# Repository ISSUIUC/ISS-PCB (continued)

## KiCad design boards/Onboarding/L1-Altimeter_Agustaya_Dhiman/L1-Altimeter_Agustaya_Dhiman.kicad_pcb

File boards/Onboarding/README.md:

# Onboarding Projects

The included projects have been developed for the purpose of teaching new members about the basics of circuit design and using KiCad.

The first project includes a 555 Timer that is used to flash several LEDs in combination with an N-channel MOSFET. This project is accompanied by other onboarding materials which explain how to use the 555 Timer and develop the circuit. There are also videos going through the [schematic](https://youtu.be/EWncukrDE1s) and [layout](https://youtu.be/gsBfX4-ESjE) design.

The second project is a basic two layer altimeter that could be used in an L1 rocket. It is intended to be more open-ended, and the included design can serve as merely an example. The altimeter includes an MCU, sensors connected via the SPI and I2C communication protocols, a microSD card for data storage, and basic power circuitry that can be used with an external voltage regulator. Extra GPIOs are broken out for future expansions.

# Schematics

Printable PDF schematics can be found in the folders for their respective boards.

# Renders

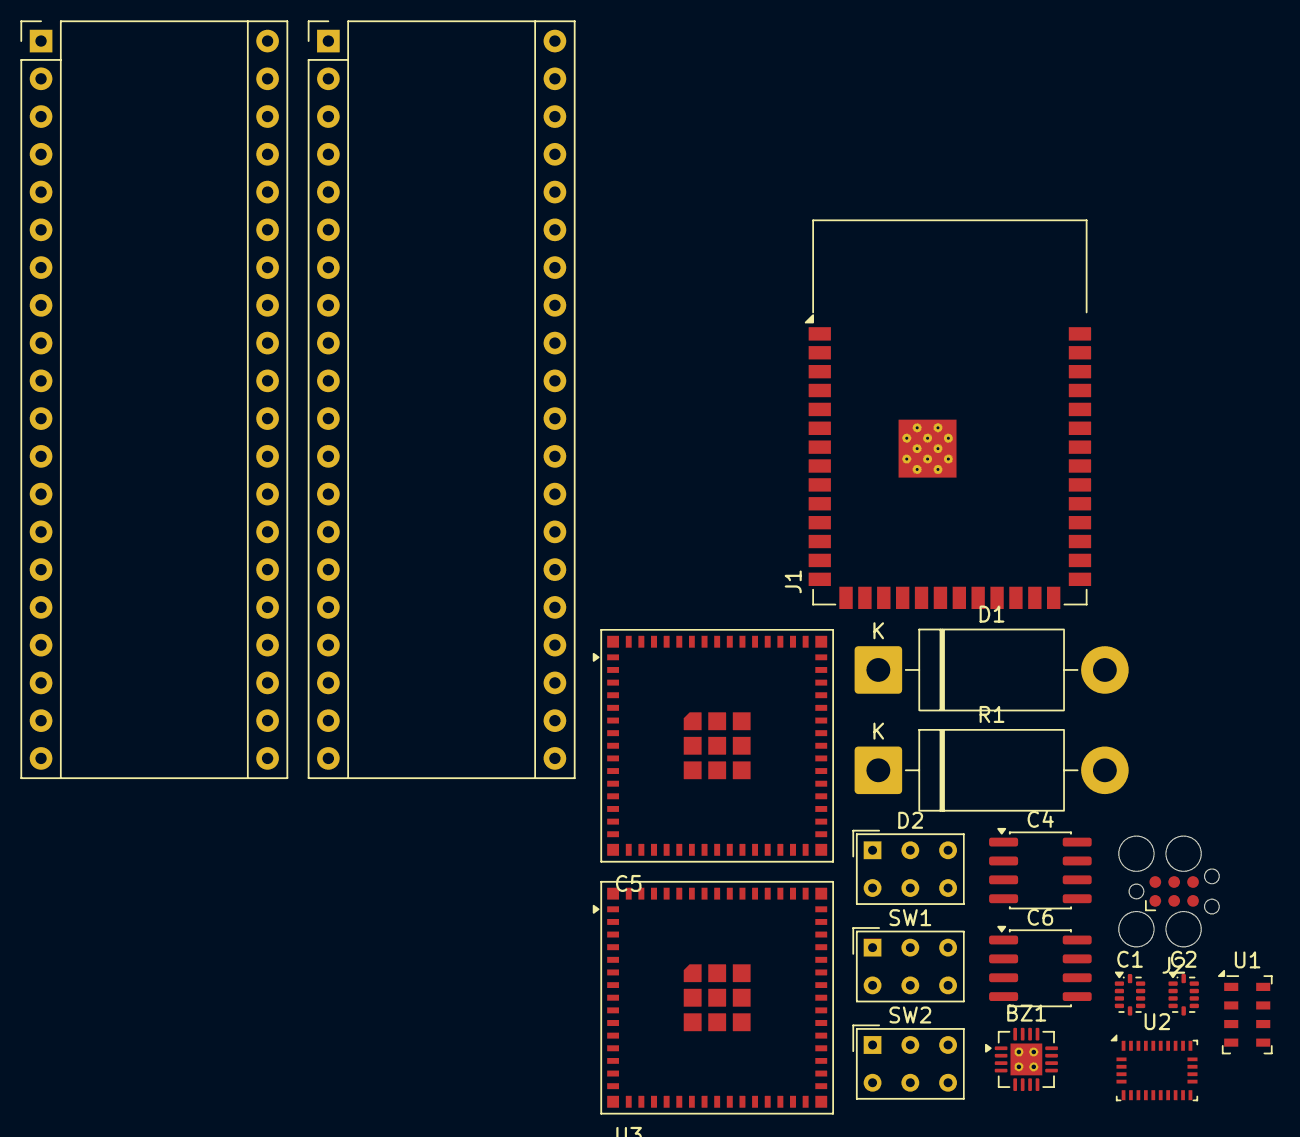
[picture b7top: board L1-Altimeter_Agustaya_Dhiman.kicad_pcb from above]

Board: 2 copper layers, 18 parts (0 on the bottom side), 9 nets, no tracks yet.

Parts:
BZ1: Buzzer; Texas_RVA_VQFN-16-1EP_3.5x3.5mm_P0.5mm_EP2.14x2.14mm_Therma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
C1, C2: .1uF; Balun_Johanson_0900PC15J0013
C4, C6: .1uF; SOIC-8_3.9x4.9mm_P1.27mm
C5: .1uF; ESP32-S2-MINI-1U
D1: MBR340; D_DO-201AD_P15.24mm_Horizontal
D2: LED; SW_NKK_GW12LJP
H1: MountingHole; Maple_Mini
J1: USB_A; ESP32-S3-WROOM-1
J2: Screw_Terminal_01x04; Tag-Connect_TC2030-IDC-FP_2x03_P1.27mm_Vertical
J10: DM3D-SF; Maple_Mini
R1: 100K; D_DO-201AD_P15.24mm_Horizontal
SW1, SW2: SW_Push; SW_NKK_GW12LJP
U1: MS5611-01BA; LGA-8_3x5mm_P1.25mm
U2: BNO086; LGA-28_5.2x3.8mm_P0.5mm
U3: ESP32-S3-MINI-1U; ESP32-S2-MINI-1U

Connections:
+3.3V: C6.1, U2.3 (VDD), U2.5 (PS1), U2.28 (VDDIO)
+3V3: C4.1, J10.4 (VDD), U1.1 (VDD), U1.2 (PS), U2.10 (CLKSEL0)
/BOOT_SW: C1.1, SW1.1
/RESET_SW: C2.1, SW2.1
/VBUS: D1.2 (A), J1.1 (VBUS), R1.1
/VSYS: D1.1 (K), J2.2
GND: BZ1.2 (-), C1.2, C2.2, C4.2, C5.2, D2.1 (K), J1.4 (GND), J2.4, J10.6 (VSS), R1.2, SW1.2, SW2.2, U1.3 (GND), U1.4 (CSB), U1.5 (CSB), U2.2 (GND), U2.25 (GNDIO)
unnamed: C5.1, U2.9 (CAP)
unnamed: U3.1 (GND), U3.2 (GND), U3.42 (GND), U3.43 (GND), U3.46 (GND), U3.47 (GND), U3.48 (GND), U3.49 (GND), U3.50 (GND), U3.51 (GND), U3.52 (GND), U3.53 (GND), U3.54 (GND), U3.55 (GND), U3.56 (GND), U3.57 (GND), U3.58 (GND), U3.59 (GND), U3.60 (GND), U3.61 (GND), U3.62 (GND), U3.63 (GND), U3.64 (GND), U3.65 (GND)

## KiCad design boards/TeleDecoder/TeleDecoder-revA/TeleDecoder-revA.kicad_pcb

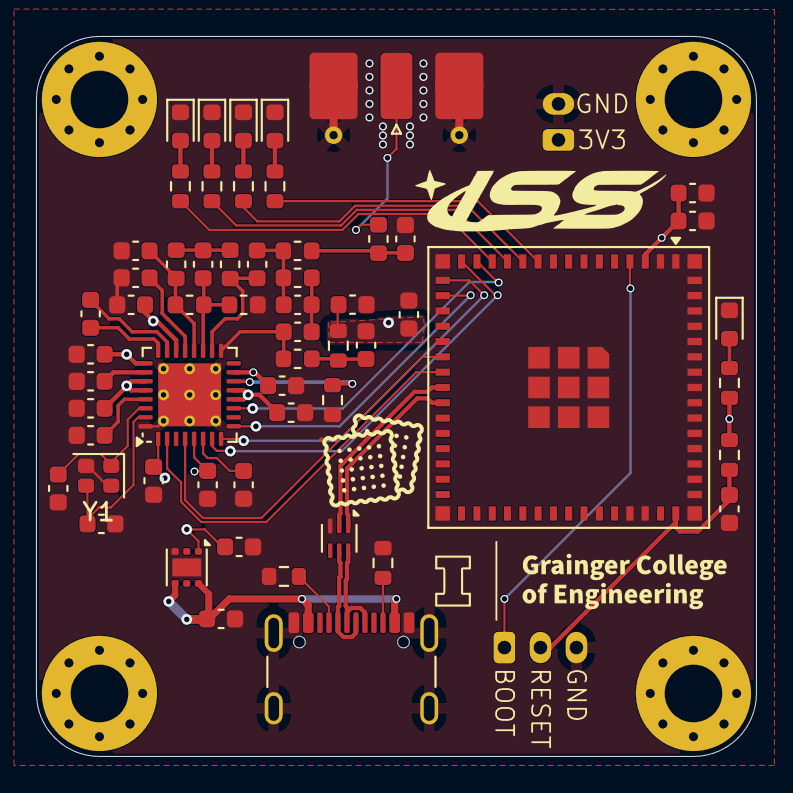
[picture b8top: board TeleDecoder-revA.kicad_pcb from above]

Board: 4 copper layers, 40.0 x 40.0 mm, 64 parts (0 on the bottom side), 45 nets.

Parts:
C1, C2, C127: 1uF; C_0603_1608Metric
C101: 22uF; C_0603_1608Metric
C102: 100nF; C_0603_1608Metric
C103, C119: 10nF; C_0603_1608Metric
C104: 56pF; C_0603_1608Metric
C105: 100pF; C_0603_1608Metric
C106: 39pF; C_0603_1608Metric
C107: 2.2pF; C_0603_1608Metric
C108, C109: 10pF; C_0603_1608Metric
C110, C111, C113: 5.1pF; C_0603_1608Metric
C112: 1.8nF; C_0603_1608Metric
C114: 6.2pF; C_0603_1608Metric
C115, C117, C118, C120, C121, C122, C123, C124, C125: 47nF; C_0603_1608Metric
C116: 220nF; C_0603_1608Metric
D101, D105: LED_RED; LED_0603_1608Metric
D102: LED_BLUE; LED_0603_1608Metric
D103: LED_GREEN; LED_0603_1608Metric
D104: LED_ORANGE; LED_0603_1608Metric
H101, H102, H103, H104: MountingHole; MountingHole_3.2mm_M3_Pad_Via
J101: Conn_01x03; JST_PH_B3B-PH-K_1x03_P2.00mm_Vertical
J102: USB4105-GF-A; USB_C_Receptacle_GCT_USB4105-xx-A_16P_TopMnt_Horizontal
J103: Conn_01x02; JST_PH_B2B-PH-K_1x02_P2.00mm_Vertical
J104: Conn_Coaxial; SMA_Molex_73251-2120_EdgeMount_Horizontal
L101, L102: 56nH; L_0603_1608Metric
L103, L106: 15nH; L_0603_1608Metric
L104, L105: 27nH; L_0603_1608Metric
L107: 43nH; L_0603_1608Metric
L108: 22nH; L_0603_1608Metric
R101, R102: 5.1k; R_0603_1608Metric
R103: 18; R_0603_1608Metric
R104: 56k; R_0603_1608Metric
R105, R106, R107, R108, R110: 470; R_0603_1608Metric
R109: 20k; R_0603_1608Metric
U101: ESP32-S3-MINI-1U; ESP32-S2-MINI-1U
U102: ECMF02-2AMX6; ST_UQFN-6L_1.5x1.7mm_P0.5mm
U103: CC1120; VQFN-32-1EP_5x5mm_P0.5mm_EP3.5x3.5mm_ThermalVias
U104: TPS746-Q1; WSON-6-1EP_2x2mm_P0.65mm_EP1x1.6mm
Y1: STDCZS3-40M; Crystal_SMD_2016-4Pin_2.0x1.6mm

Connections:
+3V3: C2.1, C101.1, C102.1, C103.1, C104.2, C105.1, C115.1, C117.1, C118.1, C120.1, C121.1, C123.1, C124.1, J103.1, R103.2, R109.2, R110.1, U101.3 (3V3), U103.1 (VDD_GUARD), U103.5 (DVDD), U103.12 (DVDD), U103.13 (AVDD_IF), U103.15 (AVDD_RF), U103.22 (AVDD_SYNTH1), U103.25 (AVDD_PFD_CHP), U103.27 (AVDD_SYNTH2), U103.28 (AVDD_XOSC), U104.1 (OUT)
+5V: C1.1, J102.A4 (VBUS), J102.A9 (VBUS), J102.B4 (VBUS), J102.B9 (VBUS), U104.4 (EN), U104.6 (IN)
/BOOT: J101.1, U101.4 (IO0)
/CS_RADIO: U101.14 (IO10), U103.11 (~CS)
/D+: J102.A6 (D+), J102.B6 (D+), U102.6 (D+_out)
/D-: J102.A7 (D-), J102.B7 (D-), U102.5 (D-_out)
/LED_BLUE: R106.1, U101.13 (IO9)
/LED_GREEN: R107.1, U101.12 (IO8)
/LED_ORANGE: R108.1, U101.11 (IO7)
/LED_RED: R105.1, U101.10 (IO6)
/LNA_N: C111.1, L102.2, L105.1, U103.20 (LNA_N)
/LNA_P: C110.1, L102.1, L104.1, U103.19 (LNA_P)
/MISO0: U101.17 (IO13), U103.9 (SO(GPIO1))
/MOSI0: U101.15 (IO11), U103.7 (SI)
/PA: C106.1, L101.1, U103.17 (PA)
/RADIO_INT: U101.21 (IO17), U103.4 (GPIO2)
/RESET: C127.1, J101.2, R109.1, U101.45 (EN)
/RESET_IN: U101.22 (IO18), U103.2 (~RESET)
/SCLK0: U101.16 (IO12), U103.8 (SCLK)
/TRX_SW: C113.1, L106.1, U103.18 (TRX_SW)
/USB_D+: U101.24 (USB_D+), U102.1 (D+_in)
/USB_D-: U101.23 (USB_D-), U102.2 (D-_in)
GND: C1.2, C2.2, C101.2, C102.2, C103.2, C105.2, C108.2, C109.2, C111.2, C114.2, C115.2, C116.2, C117.2, C118.2, C119.2, C120.2, C121.2, C122.2, C123.2, C124.2, C125.2, C127.2, D101.1 (K), D102.1 (K), D103.1 (K), D104.1 (K), D105.1 (K), J101.3, J102.A1 (GND), J102.A12 (GND), J102.B1 (GND), J102.B12 (GND), J102.S1 (SHIELD), J103.2, J104.2 (Ext), L104.2, R101.2, R102.2, R104.2, U101.1 (GND), U101.2 (GND), U101.42 (GND), U101.43 (GND), U101.46 (GND), U101.47 (GND), U101.48 (GND), U101.49 (GND), U101.50 (GND), U101.51 (GND), U101.52 (GND), U101.53 (GND), U101.54 (GND), U101.55 (GND), U101.56 (GND), U101.57 (GND), U101.58 (GND), U101.59 (GND), U101.60 (GND), U101.61 (GND), U101.62 (GND), U101.63 (GND), U101.64 (GND), U101.65 (GND), U102.3 (GND), U103.32 (EXT_XOSC), U103.33 (GND_EP), U104.3 (GND), U104.7 (EP), Y1.2
unnamed: C104.1, L101.2, R103.1
unnamed: C106.2, C107.1, L103.1
unnamed: C107.2, C113.2, L103.2, L107.1
unnamed: C110.2, L105.2, L106.2
unnamed: C114.1, L107.2, L108.1
unnamed: D101.2 (A), R105.2
unnamed: D102.2 (A), R106.2
unnamed: D103.2 (A), R107.2
unnamed: D104.2 (A), R108.2
unnamed: D105.2 (A), R110.2
unnamed: J102.A5 (CC1), R101.1
unnamed: J102.B5 (CC2), R102.1
unnamed: J104.1 (In), L108.2
unnamed: C116.1, U103.6 (DCPL)
unnamed: C122.1, U103.26 (DCPL_PFD_CHP)
unnamed: C119.1, U103.21 (DCPL_VCO)
unnamed: C125.1, U103.29 (DCPL_XOSC)
unnamed: C112.1, U103.23 (LPF0)
unnamed: C112.2, U103.24 (LPF1)
unnamed: R104.1, U103.14 (RBIAS)
unnamed: C108.1, U103.30 (XOSC_Q1), Y1.1
unnamed: C109.1, U103.31 (XOSC_Q2), Y1.3

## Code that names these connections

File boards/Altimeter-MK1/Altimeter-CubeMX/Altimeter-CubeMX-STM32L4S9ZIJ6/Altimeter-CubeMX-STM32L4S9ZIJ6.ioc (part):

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Mcu.Name=STM32L4S9ZIJx
Mcu.Package=UFBGA144
Mcu.UserName=STM32L4S9ZIJx
PA0.GPIOParameters=GPIO_Label
PA0.GPIO_Label=sense_e
PA0.Signal=ADCx_IN5
PA1.GPIOParameters=GPIO_Label
PA1.GPIO_Label=sense_f
PA1.Signal=ADCx_IN6
PA10.GPIOParameters=GPIO_Label
PA10.GPIO_Label=TELEM_CS
PA10.Signal=GPIO_Output
PA11.GPIOParameters=GPIO_Label
PA11.GPIO_Label=USB_DM
PA11.Mode=Device_Only
PA11.Signal=USB_OTG_FS_DM
PA12.GPIOParameters=GPIO_Label
PA12.GPIO_Label=USB_DP
PA12.Mode=Device_Only
PA12.Signal=USB_OTG_FS_DP
PA13\ (JTMS/SWDIO).GPIOParameters=GPIO_Label
PA13\ (JTMS/SWDIO).GPIO_Label=SWDIO
PA13\ (JTMS/SWDIO).Mode=Trace_Asynchronous_SW
PA13\ (JTMS/SWDIO).Signal=SYS_JTMS-SWDIO
PA14\ (JTCK/SWCLK).GPIOParameters=GPIO_Label
PA14\ (JTCK/SWCLK).GPIO_Label=SWSCLK
PA14\ (JTCK/SWCLK).Mode=Trace_Asynchronous_SW
PA14\ (JTCK/SWCLK).Signal=SYS_JTCK-SWCLK
PA15\ (JTDI).GPIOParameters=GPIO_Label
PA15\ (JTDI).GPIO_Label=RESERVED_JTDI
PA15\ (JTDI).Signal=SYS_JTDI
PA2.GPIOParameters=GPIO_Label
PA2.GPIO_Label=sense_vFlight
PA2.Signal=ADCx_IN7
PA3.GPIOParameters=GPIO_Label
PA3.GPIO_Label=sense_vPyro
PA3.Signal=ADCx_IN8
PA8.GPIOParameters=GPIO_Label
PA8.GPIO_Label=RESERVED_TIM1_CH1_PWM
PA8.Signal=S_TIM1_CH1
PA9.GPIOParameters=GPIO_Label
PA9.GPIO_Label=RESERVED_TIM1_CH2_PWM
PA9.Signal=S_TIM1_CH2
PB10.GPIOParameters=GPIO_Label
PB10.GPIO_Label=TELEM_SCK
PB10.Mode=Full_Duplex_Master
PB10.Signal=SPI2_SCK
PB15.GPIOParameters=GPIO_Label
PB15.GPIO_Label=TELEM_MOSI
PB15.Mode=Full_Duplex_Master
PB15.Signal=SPI2_MOSI
PB2.GPIOParameters=GPIO_Label
PB2.GPIO_Label=BUZZER_PWM
PB2.Mode=WaveformGeneration
PB2.Signal=LPTIM1_OUT
PB3\ (JTDO/TRACESWO).GPIOParameters=GPIO_Label
PB3\ (JTDO/TRACESWO).GPIO_Label=SWO
PB3\ (JTDO/TRACESWO).Mode=Trace_Asynchronous_SW
PB3\ (JTDO/TRACESWO).Signal=SYS_JTDO-SWO
PB4\ (NJTRST).GPIOParameters=GPIO_Label
PB4\ (NJTRST).GPIO_Label=RESERVED_PB4
PB4\ (NJTRST).Signal=SYS_JTRST
PB5.GPIOParameters=GPIO_Label
PB5.GPIO_Label=RESERVED_TIM3_CH2_PWM
PB5.Signal=S_TIM3_CH2
PB6.GPIOParameters=GPIO_Label
PB6.GPIO_Label=RESERVED_USART1_TX
PB6.Mode=Multiprocessor_communication
PB6.Signal=USART1_TX
PB7.GPIOParameters=GPIO_Label
PB7.GPIO_Label=RESERVED_USART1_RX
PB7.Mode=Multiprocessor_communication
PB7.Signal=USART1_RX
PB8.GPIOParameters=GPIO_Label
PB8.GPIO_Label=LED_BLUE
PB8.Signal=GPIO_Output
PB9.GPIOParameters=GPIO_Label
PB9.GPIO_Label=LED_ORANGE
PB9.Signal=GPIO_Output
PC0.GPIOParameters=GPIO_Label
PC0.GPIO_Label=sense_a
PC0.Signal=ADCx_IN1
PC1.GPIOParameters=GPIO_Label
PC1.GPIO_Label=sense_b
PC1.Signal=ADCx_IN2
PC10.GPIOParameters=GPIO_Label
PC10.GPIO_Label=RESERVED_SDMMC1_D2
PC10.Mode=SD_4_bits_Wide_bus
PC10.Signal=SDMMC1_D2
PC11.GPIOParameters=GPIO_Label
PC11.GPIO_Label=RESERVED_SDMMC1_D3
PC11.Mode=SD_4_bits_Wide_bus
PC11.Signal=SDMMC1_D3
PC12.GPIOParameters=GPIO_Label
PC12.GPIO_Label=RESERVED_SDMMC1_CK
PC12.Mode=SD_4_bits_Wide_bus
PC12.Signal=SDMMC1_CK
PC13.GPIOParameters=GPIO_Label
PC13.GPIO_Label=LSM9DS1_INT2_A/G
PC13.Signal=GPIO_Input
PC14-OSC32_IN\ (PC14).GPIOParameters=GPIO_Label
PC14-OSC32_IN\ (PC14).GPIO_Label=TELEM_GPIO_5
PC14-OSC32_IN\ (PC14).Signal=GPIO_Input
PC15-OSC32_OUT\ (PC15).GPIOParameters=GPIO_Label
PC15-OSC32_OUT\ (PC15).GPIO_Label=TELEM_GPIO_4
PC15-OSC32_OUT\ (PC15).Signal=GPIO_Input
PC2.GPIOParameters=GPIO_Label
PC2.GPIO_Label=sense_c
PC2.Signal=ADCx_IN3
PC3.GPIOParameters=GPIO_Label
PC3.GPIO_Label=sense_d
PC3.Signal=ADCx_IN4
PC6.GPIOParameters=GPIO_Label,GPIO_Mode
PC6.GPIO_Label=TELEM_INT
PC6.GPIO_Mode=GPIO_MODE_INPUT
PC6.Signal=GPIO_Input
PC7.GPIOParameters=GPIO_Label,GPIO_Mode
PC7.GPIO_Label=SAM-M8Q_EXTINT
PC7.GPIO_Mode=GPIO_MODE_INPUT
PC7.Signal=GPIO_Input
PC8.GPIOParameters=GPIO_Label
PC8.GPIO_Label=RESERVED_SDMMC1_D0
PC8.Mode=SD_4_bits_Wide_bus
PC8.Signal=SDMMC1_D0
PC9.GPIOParameters=GPIO_Label
PC9.GPIO_Label=RESERVED_SDMMC1_D1
PC9.Mode=SD_4_bits_Wide_bus
PC9.Signal=SDMMC1_D1
PD0.GPIOParameters=GPIO_Label
PD0.GPIO_Label=FMC_D2
PD0.Signal=FMC_D2_DA2
PD1.GPIOParameters=GPIO_Label
PD1.GPIO_Label=FMC_D3
PD1.Signal=FMC_D3_DA3
PD11.GPIOParameters=GPIO_Label
PD11.GPIO_Label=FMC_CLE
PD11.Signal=FMC_A16_CLE
PD12.GPIOParameters=GPIO_Label
PD12.GPIO_Label=FMC_ALE
PD12.Signal=FMC_A17_ALE
PD14.GPIOParameters=GPIO_Label
PD14.GPIO_Label=FMC_D0
PD14.Signal=FMC_D0_DA0
PD15.GPIOParameters=GPIO_Label
PD15.GPIO_Label=FMC_D1
PD15.Signal=FMC_D1_DA1
PD2.GPIOParameters=GPIO_Label
PD2.GPIO_Label=RESERVED_SDMMC1_CMD
PD2.Mode=SD_4_bits_Wide_bus
PD2.Signal=SDMMC1_CMD
PD3.GPIOParameters=GPIO_Label
PD3.GPIO_Label=TELEM_MISO
PD3.Mode=Full_Duplex_Master
PD3.Signal=SPI2_MISO
PD4.GPIOParameters=GPIO_Label
PD4.GPIO_Label=FMC_RE
PD4.Signal=FMC_NOE
PD5.GPIOParameters=GPIO_Label
PD5.GPIO_Label=FLASH_WE
PD5.Signal=FMC_NWE
PD6.GPIOParameters=GPIO_Label
PD6.GPIO_Label=FMC_NWAIT
PD6.Signal=FMC_NWAIT
PD7.GPIOParameters=GPIO_Label
PD7.GPIO_Label=FMC_CE
PD7.Mode=NandChipSelect3_1
PD7.Signal=FMC_NCE
PE0.GPIOParameters=GPIO_Label
PE0.GPIO_Label=LED_RED
PE0.Signal=GPIO_Output
PE1.GPIOParameters=GPIO_Label
PE1.GPIO_Label=H3LIS331DL_CS
PE1.Signal=GPIO_Output
PE10.GPIOParameters=GPIO_Label
PE10.GPIO_Label=FMC_D7
PE10.Signal=FMC_D7_DA7
PE2.GPIOParameters=GPIO_Label
PE2.GPIO_Label=MS5611_CS
PE2.Signal=GPIO_Output
PE3.GPIOParameters=GPIO_Label
PE3.GPIO_Label=RESERVED_TIM3_CH1_PWM
PE3.Signal=S_TIM3_CH1
PE4.GPIOParameters=GPIO_Label
PE4.GPIO_Label=TELEM_GPIO_3
PE4.Signal=GPIO_Input
PE5.GPIOParameters=GPIO_Label
PE5.GPIO_Label=LSM9DS1_CS_M
PE5.Signal=GPIO_Output
PE6.GPIOParameters=GPIO_Label
PE6.GPIO_Label=TELEM_GPIO_2
PE6.Signal=GPIO_Input
PE7.GPIOParameters=GPIO_Label
PE7.GPIO_Label=FMC_D4
PE7.Signal=FMC_D4_DA4
PE8.GPIOParameters=GPIO_Label
PE8.GPIO_Label=FMC_D5
PE8.Signal=FMC_D5_DA5
PE9.GPIOParameters=GPIO_Label
PE9.GPIO_Label=FMC_D6
PE9.Signal=FMC_D6_DA6
PF0.GPIOParameters=GPIO_Label
PF0.GPIO_Label=SAM-M8Q_SDA
PF0.Mode=I2C
PF0.Signal=I2C2_SDA
PF1.GPIOParameters=GPIO_Label
PF1.GPIO_Label=SAM-M8Q_SCL
PF1.Mode=I2C
PF1.Signal=I2C2_SCL
PF2.GPIOParameters=GPIO_Label
PF2.GPIO_Label=LSM9DS1_INT1_A/G
PF2.Signal=GPIO_Input
PF3.GPIOParameters=GPIO_Label
PF3.GPIO_Label=LSM9DS1_INT1_M
PF3.Signal=GPIO_Input
PF4.GPIOParameters=GPIO_Label
PF4.GPIO_Label=TELEM_RST
PF4.Signal=GPIO_Input
PF5.GPIOParameters=GPIO_Label
PF5.GPIO_Label=LED_GREEN
PF5.Signal=GPIO_Output
PF6.GPIOParameters=GPIO_Label
PF6.GPIO_Label=MCU_TPS2594_GP
PF6.Signal=GPIO_Input
PF8.GPIOParameters=GPIO_Label
PF8.GPIO_Label=LSM9DS1_DEN_A/G
PF8.Signal=GPIO_Input
PG10.GPIOParameters=GPIO_Label
PG10.GPIO_Label=H3LIS331DL_INT1
PG10.Signal=GPIO_Input
PG12.GPIOParameters=GPIO_Label
PG12.GPIO_Label=TELEM_GPIO_1
PG12.Signal=GPIO_Input
PG13.GPIOParameters=GPIO_Label
PG13.GPIO_Label=LSM9DS1_CS_A/G
PG13.Signal=GPIO_Output
PG2.GPIOParameters=GPIO_Label
PG2.GPIO_Label=SNS_SCK
PG2.Mode=Full_Duplex_Master
PG2.Signal=SPI1_SCK
PG3.GPIOParameters=GPIO_Label
PG3.GPIO_Label=SNS_MISO
PG3.Mode=Full_Duplex_Master
PG3.Signal=SPI1_MISO
PG4.GPIOParameters=GPIO_Label
PG4.GPIO_Label=SNS_MOSI
PG4.Mode=Full_Duplex_Master
PG4.Signal=SPI1_MOSI
PG7.GPIOParameters=GPIO_Label
PG7.GPIO_Label=LSM9DS1_DRDY_M
PG7.Signal=GPIO_Input
PG8.GPIOParameters=GPIO_Label
PG8.GPIO_Label=H3LIS331DL_INT2
PG8.Signal=GPIO_Input
PH0-OSC_IN\ (PH0).GPIOParameters=GPIO_Label
PH0-OSC_IN\ (PH0).GPIO_Label=HSE_CLK
PH0-OSC_IN\ (PH0).Mode=HSE-External-Clock-Source
PH0-OSC_IN\ (PH0).Signal=RCC_OSC_IN
RCC.HSE_VALUE=8000000
RCC.SYSCLKFreq_VALUE=120000000
RCC.SYSCLKSource=RCC_SYSCLKSOURCE_PLLCLK
board=custom

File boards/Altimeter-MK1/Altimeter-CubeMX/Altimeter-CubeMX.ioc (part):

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Mcu.Name=STM32U585QIIx
Mcu.Package=UFBGA132
Mcu.UserName=STM32U585QIIx
PA0.GPIOParameters=GPIO_Label
PA0.GPIO_Label=RESERVED_TIM5_CH1_PWM
PA0.Signal=S_TIM5_CH1
PA1.GPIOParameters=GPIO_Label
PA1.GPIO_Label=SNS_SCK
PA1.Mode=Full_Duplex_Master
PA1.Signal=SPI1_SCK
PA11.GPIOParameters=GPIO_Label
PA11.GPIO_Label=USB_DM
PA11.Mode=Device_Only
PA11.Signal=USB_OTG_FS_DM
PA12.GPIOParameters=GPIO_Label
PA12.GPIO_Label=USB_DP
PA12.Mode=Device_Only
PA12.Signal=USB_OTG_FS_DP
PA13\ (JTMS/SWDIO).GPIOParameters=GPIO_Label
PA13\ (JTMS/SWDIO).GPIO_Label=SWDIO
PA13\ (JTMS/SWDIO).Mode=Trace_Asynchronous_SW
PA13\ (JTMS/SWDIO).Signal=DEBUG_JTMS-SWDIO
PA14\ (JTCK/SWCLK).GPIOParameters=GPIO_Label
PA14\ (JTCK/SWCLK).GPIO_Label=SWCLK
PA14\ (JTCK/SWCLK).Mode=Trace_Asynchronous_SW
PA14\ (JTCK/SWCLK).Signal=DEBUG_JTCK-SWCLK
PA15\ (JTDI).GPIOParameters=GPIO_Label
PA15\ (JTDI).GPIO_Label=RESERVED_CC1/JTDI
PA15\ (JTDI).Mode=Sink_AllSignals
PA15\ (JTDI).Signal=UCPD1_CC1
PA4.GPIOParameters=GPIO_Label
PA4.GPIO_Label=MCU_TPS2594_GP
PA4.Signal=GPIO_Input
PA7.GPIOParameters=GPIO_Label
PA7.GPIO_Label=LSM9DS1_DRDY_M
PA7.Signal=GPIO_Input
PA8.GPIOParameters=GPIO_Label
PA8.GPIO_Label=LSM9DS1_DEN_A/G
PA8.Signal=GPIO_Input
PB15.GPIOParameters=GPIO_Label
PB15.GPIO_Label=RESERVED_CC2
PB15.Mode=Sink_AllSignals
PB15.Signal=UCPD1_CC2
PB3\ (JTDO/TRACESWO).GPIOParameters=GPIO_Label
PB3\ (JTDO/TRACESWO).GPIO_Label=SWO
PB3\ (JTDO/TRACESWO).Mode=Trace_Asynchronous_SW
PB3\ (JTDO/TRACESWO).Signal=DEBUG_JTDO-SWO
PB4\ (NJTRST).GPIOParameters=GPIO_Label
PB4\ (NJTRST).GPIO_Label=RESERVED_JTRST
PB4\ (NJTRST).Signal=DEBUG_JTRST
PB5.GPIOParameters=GPIO_Label
PB5.GPIO_Label=SNS_MOSI
PB5.Mode=Full_Duplex_Master
PB5.Signal=SPI1_MOSI
PB6.GPIOParameters=GPIO_Label
PB6.GPIO_Label=SAM-M8Q_SCL
PB6.Mode=I2C
PB6.Signal=I2C1_SCL
PB7.GPIOParameters=GPIO_Label
PB7.GPIO_Label=SAM-M8Q_EXTINT
PB7.Signal=GPIO_Input
PB9.GPIOParameters=GPIO_Label
PB9.GPIO_Label=SAM-MAQ-SDA
PB9.Mode=I2C
PB9.Signal=I2C1_SDA
PC0.GPIOParameters=GPIO_Label
PC0.GPIO_Label=sense_a
PC0.Mode=IN1
PC0.Signal=ADC4_IN1
PC1.GPIOParameters=GPIO_Label
PC1.GPIO_Label=sense_b
PC1.Mode=IN2
PC1.Signal=ADC4_IN2
PC11.GPIOParameters=GPIO_Label
PC11.GPIO_Label=TELEM_MISO
PC11.Mode=Full_Duplex_Master
PC11.Signal=SPI3_MISO
PC12.GPIOParameters=GPIO_Label
PC12.GPIO_Label=TELEM_MOSI
PC12.Mode=Full_Duplex_Master
PC12.Signal=SPI3_MOSI
PC2.GPIOParameters=GPIO_Label
PC2.GPIO_Label=sense_c
PC2.Mode=IN3
PC2.Signal=ADC4_IN3
PC3.GPIOParameters=GPIO_Label
PC3.GPIO_Label=sense_d
PC3.Mode=IN4
PC3.Signal=ADC4_IN4
PC6.GPIOParameters=GPIO_Label
PC6.GPIO_Label=RESERVED_TIM8_CH1_PWM
PC6.Signal=S_TIM8_CH1
PD0.GPIOParameters=GPIO_Label
PD0.GPIO_Label=FMC_D2
PD0.Signal=FMC_D2_DA2
PD1.GPIOParameters=GPIO_Label
PD1.GPIO_Label=FMC_D3
PD1.Signal=FMC_D3_DA3
PD11.GPIOParameters=GPIO_Label
PD11.GPIO_Label=FMC_CLE
PD11.Signal=FMC_A16_CLE
PD12.GPIOParameters=GPIO_Label
PD12.GPIO_Label=FMC_ALE
PD12.Signal=FMC_A17_ALE
PD14.GPIOParameters=GPIO_Label
PD14.GPIO_Label=FMC_D0
PD14.Signal=FMC_D0_DA0
PD15.GPIOParameters=GPIO_Label
PD15.GPIO_Label=FMC_D1
PD15.Signal=FMC_D1_DA1
PD4.GPIOParameters=GPIO_Label
PD4.GPIO_Label=FMC_RE
PD4.Signal=FMC_NOE
PD5.GPIOParameters=GPIO_Label
PD5.GPIO_Label=FMC_WE
PD5.Signal=FMC_NWE
PD6.GPIOParameters=GPIO_Label
PD6.GPIO_Label=FMC_NWAIT
PD6.Signal=FMC_NWAIT
PD7.GPIOParameters=GPIO_Label
PD7.GPIO_Label=FMC_CE
PD7.Mode=NandChipSelect3_1
PD7.Signal=FMC_NCE
PE10.GPIOParameters=GPIO_Label
PE10.GPIO_Label=FMC_D7
PE10.Signal=FMC_D7_DA7
PE11.GPIOParameters=GPIO_Label
PE11.GPIO_Label=TELEM_GPIO_5
PE11.Signal=GPIO_Input
PE12.GPIOParameters=GPIO_Label
PE12.GPIO_Label=TELEM_GPIO_4
PE12.Signal=GPIO_Input
PE13.GPIOParameters=GPIO_Label
PE13.GPIO_Label=TELEM_GPIO_3
PE13.Signal=GPIO_Input
PE14.GPIOParameters=GPIO_Label
PE14.GPIO_Label=TELEM_GPIO_2
PE14.Signal=GPIO_Input
PE15.GPIOParameters=GPIO_Label
PE15.GPIO_Label=TELEM_GPIO_1
PE15.Signal=GPIO_Output
PE2.GPIOParameters=GPIO_Label
PE2.GPIO_Label=LED_RED
PE2.Signal=GPIO_Output
PE3.GPIOParameters=GPIO_Label
PE3.GPIO_Label=LED_ORANGELED_ORANGE
PE3.Signal=GPIO_Output
PE4.GPIOParameters=GPIO_Label
PE4.GPIO_Label=BUZZER_PWM
PE4.Signal=S_TIM3_CH2
PE5.GPIOParameters=GPIO_Label
PE5.GPIO_Label=LED_GREEN
PE5.Signal=GPIO_Output
PE6.GPIOParameters=GPIO_Label
PE6.GPIO_Label=LED_BLUE
PE6.Signal=GPIO_Output
PE7.GPIOParameters=GPIO_Label
PE7.GPIO_Label=FMC_D4
PE7.Signal=FMC_D4_DA4
PE8.GPIOParameters=GPIO_Label
PE8.GPIO_Label=FMC_D5
PE8.Signal=FMC_D5_DA5
PE9.GPIOParameters=GPIO_Label
PE9.GPIO_Label=FMC_D6
PE9.Signal=FMC_D6_DA6
PF0.GPIOParameters=GPIO_Label
PF0.GPIO_Label=LSM9DS1_CS_M
PF0.Signal=GPIO_Input
PF1.GPIOParameters=GPIO_Label
PF1.GPIO_Label=MS5611_CS
PF1.Signal=GPIO_Input
PF11.GPIOParameters=GPIO_Label
PF11.GPIO_Label=LSM9DS1_INT1_M
PF11.Signal=GPIO_Input
PF12.GPIOParameters=GPIO_Label
PF12.GPIO_Label=H3LIS331DL_INT1
PF12.Signal=GPIO_Input
PF13.GPIOParameters=GPIO_Label
PF13.GPIO_Label=H3LIS331DL_INT2
PF13.Signal=GPIO_Input
PF14.GPIOParameters=GPIO_Label
PF14.GPIO_Label=sense_e
PF14.Mode=IN5
PF14.Signal=ADC4_IN5
PF15.GPIOParameters=GPIO_Label
PF15.GPIO_Label=sense_f
PF15.Mode=IN6
PF15.Signal=ADC4_IN6
PF2.GPIOParameters=GPIO_Label
PF2.GPIO_Label=H3LIS331DL_CS
PF2.Signal=GPIO_Input
PF3.GPIOParameters=GPIO_Label
PF3.GPIO_Label=LSM9DS1_CS_A/G
PF3.Signal=GPIO_Input
PF4.GPIOParameters=GPIO_Label
PF4.GPIO_Label=LSM9DS1_INT1_A/G
PF4.Signal=GPIO_Input
PF5.GPIOParameters=GPIO_Label
PF5.GPIO_Label=LSM9DS1_INT2_A/G
PF5.Signal=GPIO_Input
PG0.GPIOParameters=GPIO_Label
PG0.GPIO_Label=sense_vFlight
PG0.Mode=IN7
PG0.Signal=ADC4_IN7
PG1.GPIOParameters=GPIO_Label
PG1.GPIO_Label=sense_vPyro
PG1.Mode=IN8
PG1.Signal=ADC4_IN8
PG10.GPIOParameters=GPIO_Label
PG10.GPIO_Label=fire_a
PG10.Signal=GPIO_Output
PG11.GPIOParameters=GPIO_Label
PG11.GPIO_Label=fire_b
PG11.Signal=GPIO_Output
PG12.GPIOParameters=GPIO_Label
PG12.GPIO_Label=fire_c
PG12.Signal=GPIO_Output
PG13.GPIOParameters=GPIO_Label
PG13.GPIO_Label=fire_d
PG13.Signal=GPIO_Output
PG14.GPIOParameters=GPIO_Label
PG14.GPIO_Label=fire_e
PG14.Signal=GPIO_Output
PG15.GPIOParameters=GPIO_Label
PG15.GPIO_Label=fire_f
PG15.Signal=GPIO_Output
PG3.GPIOParameters=GPIO_Label
PG3.GPIO_Label=SNS_MISO
PG3.Mode=Full_Duplex_Master
PG3.Signal=SPI1_MISO
PG6.GPIOParameters=GPIO_Label
PG6.GPIO_Label=TELEM_INT
PG6.Signal=GPIO_Input
PG7.GPIOParameters=GPIO_Label
PG7.GPIO_Label=TELEM_CS
PG7.Signal=GPIO_Input
PG8.GPIOParameters=GPIO_Label
PG8.GPIO_Label=TELEM_RST
PG8.Signal=GPIO_Input
PG9.GPIOParameters=GPIO_Label
PG9.GPIO_Label=TELEM_SCK
PG9.Mode=Full_Duplex_Master
PG9.Signal=SPI3_SCK
PH0-OSC_IN\ (PH0).GPIOParameters=GPIO_Label
PH0-OSC_IN\ (PH0).GPIO_Label=HSE_CLK
PH0-OSC_IN\ (PH0).Mode=HSE-External-Clock-Source
PH0-OSC_IN\ (PH0).Signal=RCC_OSC_IN
RCC.HSE_VALUE=32000000
RCC.SYSCLKFreq_VALUE=32000000
RCC.SYSCLKSource=RCC_SYSCLKSOURCE_HSE
board=custom

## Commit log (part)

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2026-01-25 drawing sheet stuff + avocado
2026-01-25 moved like one trace
2026-01-25 zones touch
2026-01-25 vias!
2026-01-25 deleted weird paste
2026-01-25 large amount of cleanup
2026-01-25 much more cleanup its pretty darn good now
2026-01-25 renamed folder to avocado
2026-01-25 switch numbers + centering LEDs
2026-01-26 fixed mcu power conn polarity
2026-01-26 Edited Borzoi board silkscreen with authors and +/- indicators.
2026-01-26 Grounded NC pins
2026-01-26 q shit oops cleaned up mcu power circuitry
2026-01-26 fixed connector polarity
2026-01-26 2oz of the most insignificant tweaks you've ever seen
2026-01-27 Fixed DRC errors and cleaned up silkscreen.
    A JST-PH and Molex Micro-Fit connector are stacked on top of each other
    for 12V power delivery. We can't currently decide which one to use. This
    makes an error in DRC but is intentional and should cause no actual
    problems.
2026-01-27 Fixed a stupid mistake
2026-01-27 Fixed another stupid mistake
2026-01-27 renamed files to avocado
2026-01-27 renaming to butter
2026-01-27 Fixed polarity on XT60s
2026-01-27 Fixed silkscreen overlap
2026-01-27 refilled zones
2026-01-27 gerbers
2026-01-27 made it pretty
2026-01-29 increasing clearance/trace width for our jlcomrades
2026-01-30 initialize TeleDecoder project
2026-01-30 Added ESP32 and LDO to schematic, need to add transceiver and SMA connector
2026-01-30 add symbols
2026-01-30 added b125185 chip schematic
2026-01-30 antenna schematic
2026-01-31 CC1120 pins
2026-01-31 40MHz crystal
2026-01-31 Added 12 MHz crystal to library
2026-01-31 Fixed 12 MHz crystal symbol
2026-01-31 symbol library
2026-01-31 removing regulator torex
2026-01-31 deleting changes out of branches scope
2026-01-31 RF transceiver schematic
2026-01-31 oops
2026-01-31 added USBC port, pd, and voltage regulator
2026-01-31 fixing merge conflict?
2026-01-31 regulator torex stuff
2026-01-31 ESP32 SPI connection
2026-01-31 Boot/Reset
2026-02-06 Finished up schematic, started layout, laid out general placement, need to finish up SMA antenna
2026-02-06 adding displays to this
2026-02-07 adding footprints, hooking up i2c busses, adding test points
2026-02-13 routing
2026-02-13 minor fixes, added ADC
2026-02-14 Routing and minor schematic fixes
2026-02-20 battery_board debug pins
2026-02-20 change gpio pins
2026-02-20 added footprints
2026-02-20 Mounting holes, rerouting
2026-02-21 added 3v3 and 5v test point
2026-02-21 switch coax footprint
2026-02-21 Debug pins, silkscreen
2026-02-21 pls fix
2026-02-21 more fixing
2026-02-21 fix for real this time
2026-02-21 Decoupling capacitor
2026-02-21 real fix this time
2026-02-21 fixing naming
2026-02-21 setting board constraints
2026-02-21 changing pinouts to be more convienent
2026-02-21 drawings
2026-02-21 grainger logo
2026-02-21 align labels
2026-02-21 routing for displays 1-3
2026-02-27 Minor changes
2026-02-27 routed the 4-6 battery chargers. started USB routing
2026-03-06 added routing for voltage regulators
2026-03-06 battery board routing stuff
2026-03-07 simplified i2c traces, board edge zone redone
2026-03-11 bom added
2026-04-04 Display Board
    Added symbol for Display board, edited pull-up resistors and microcontroller expander to match the pins on the display board symbol.
2026-04-04 Added voltage regulator
2026-04-05 lots of clean up
2026-04-05 12V7 regulator values
2026-04-06 more clean up
2026-04-06 footprints
2026-04-06 stuff
2026-04-06 idk why these are here
2026-04-09 fixes
    dnp on usbc cc lines, dnp on vset/iset and i2c on usb pd, connected d+/- for BC1.2, switched to 500 mA ldo, 500 mA charging and decoupling caps on bat charger
2026-04-09 battery charger fp
2026-04-09 some layout started
2026-04-09 mounting holes
2026-04-09 display 3d model but it kinda sucks
2026-04-10 new routing on MCU, ADC, and the votlage regulators
2026-04-10 Implemented new gnss
2026-04-12 INIT
2026-04-12 init new transciever symbol under transceiver nice rf and init cam revC
2026-04-12 Finished new transciever
2026-04-12 18 ohm resistor value
2026-04-12 Switched Si4463 with LR2021 in Schematic
2026-04-12 SYMBOL / Schematic
2026-04-12 initial layout for connections between MCU, display, USB C PD, Chargers and Regulators
2026-04-12 fnished transciever footprint
2026-04-12 hided gnd
2026-04-12 added footprint
2026-04-12 updated lr2021 footprint
2026-04-12 more stuff
2026-04-12 routed new transciever
2026-04-12 zone fill
2026-04-12 minor wire
2026-04-13 ROUTING DONE
    New LR2021 Footprint Integration
2026-04-13 drc passes
2026-04-14 silkscreen
2026-04-14 edge cuts
2026-04-15 EAGLE REVB + EAGLE A (w/ w/o amp)
2026-04-15 minor routing tweaks
2026-04-15 changed cap fp
2026-04-15 removed sus pf cap
2026-04-15 another cap fp
2026-04-15 fixed some drc stuff
2026-04-15 drc deleted random unconnected
2026-04-15 deleted references slikscreen
2026-04-15 names on board
2026-04-15 fixed sma footprint
2026-04-16 xt60
2026-04-16 adjusted xt60
2026-04-25 deleting stuff out of branch scope
2026-04-25 date in comments
2026-05-22 Fixed bad wiring and changed 5V regs
2026-05-25 Fixed output inductor values
2026-05-25 Added more output capacitors
2026-05-26 borzoi v3.1
